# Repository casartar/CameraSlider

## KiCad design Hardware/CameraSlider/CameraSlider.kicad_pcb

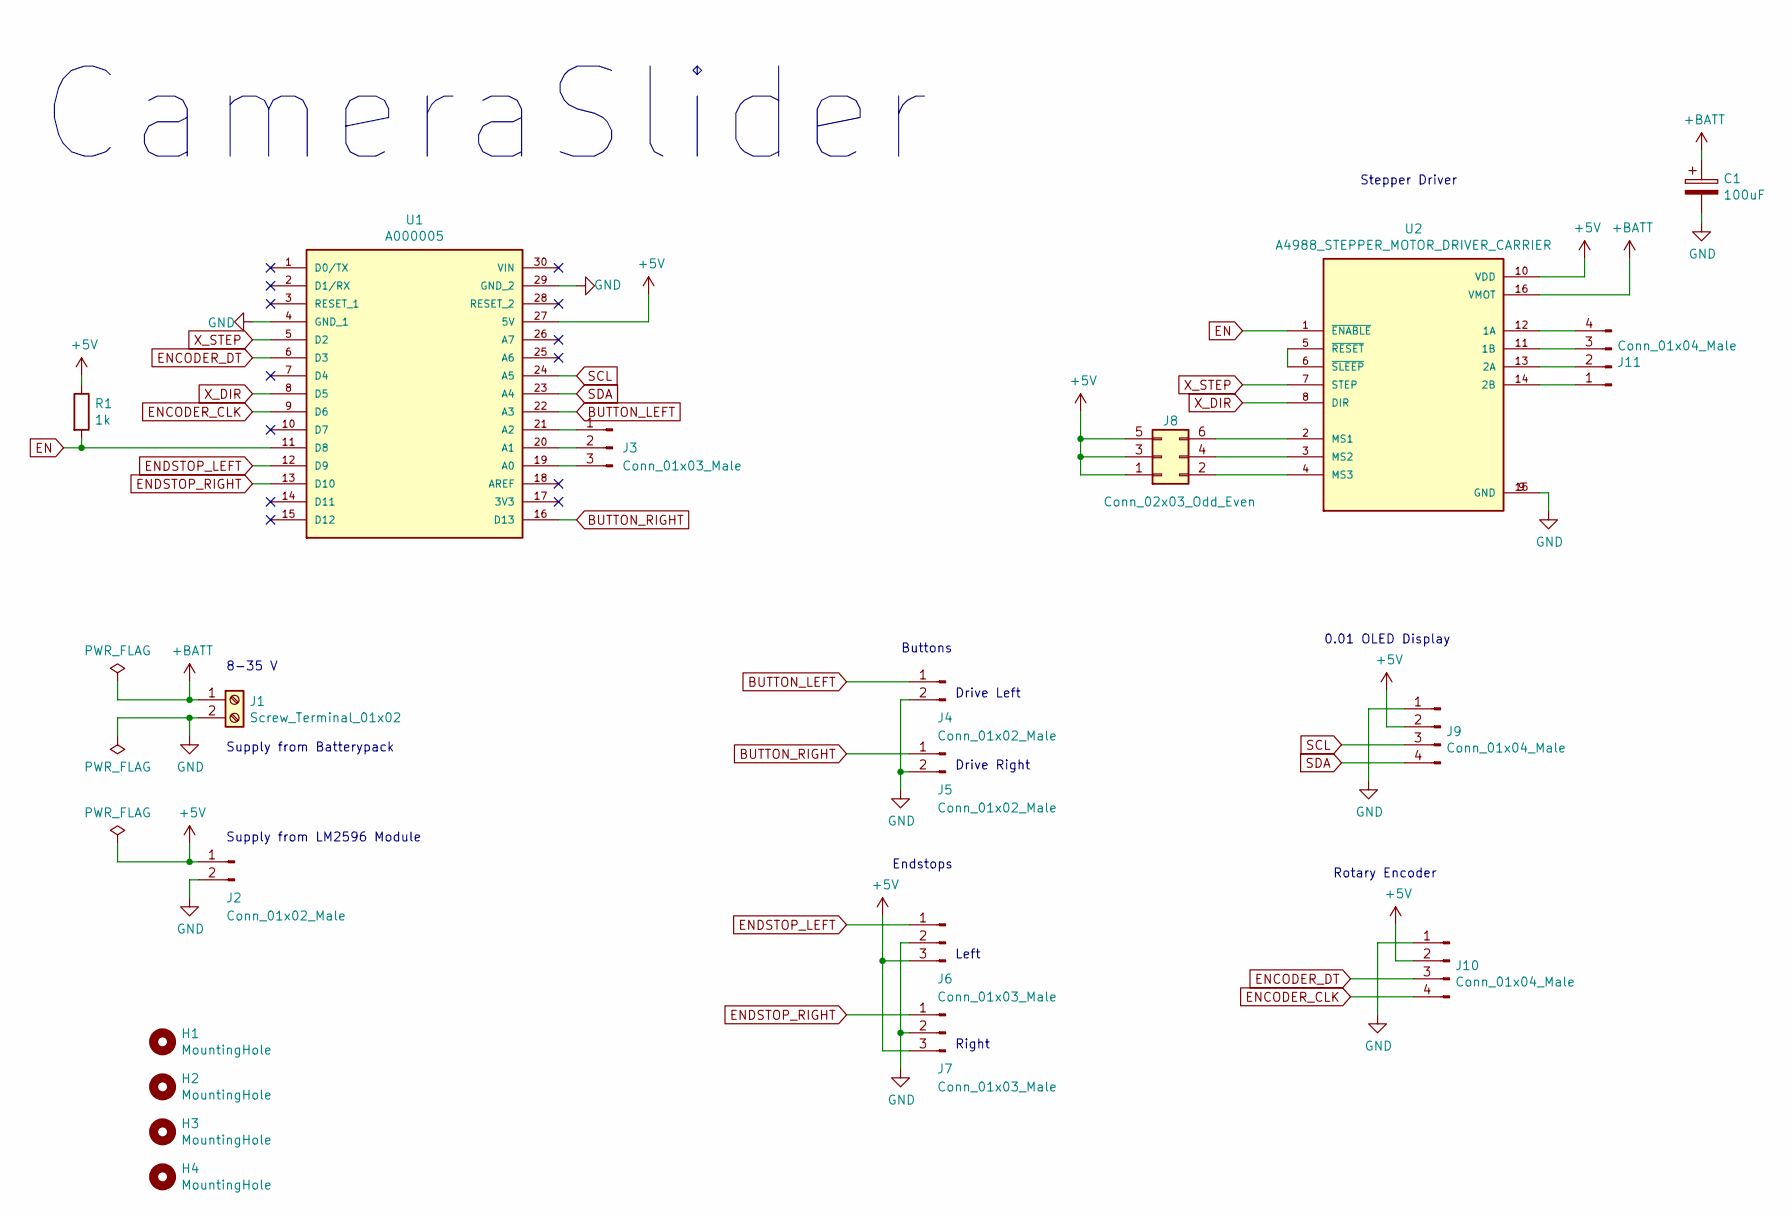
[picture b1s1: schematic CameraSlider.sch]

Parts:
C1: 100uF; CP_Radial_D8.0mm_P2.50mm
H1, H2, H3, H4: MountingHole; MountingHole_3.2mm_M3_Pad
J1: Screw_Terminal_01x02; TerminalBlock_Altech_AK300-2_P5.00mm
J2, J4, J5: Conn_01x02_Male; Pin_Header_Angled_1x02_Pitch2.54mm
J3: Conn_01x03_Male; Pin_Header_Straight_1x03_Pitch2.54mm
J6, J7: Conn_01x03_Male; Pin_Header_Angled_1x03_Pitch2.54mm
J8: Conn_02x03_Odd_Even; Pin_Header_Straight_2x03_Pitch2.54mm
J9, J10, J11: Conn_01x04_Male; Pin_Header_Angled_1x04_Pitch2.54mm
R1: 1k; R_Axial_DIN0207_L6.3mm_D2.5mm_P7.62mm_Horizontal
U1: A000005; MODULE_A000005; PARTREV 23/03/2020
U2: A4988_STEPPER_MOTOR_DRIVER_CARRIER; MODULE_A4988_STEPPER_MOTOR_DRIVER_CARRIER

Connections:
+5V: J2.1, J6.3, J7.3, J8.1, J8.3, J8.5, J9.2, J10.2, R1.1, U1.27 (5V), U2.10 (VDD)
+BATT: C1.1, J1.1, U2.16 (VMOT)
BUTTON_LEFT: J4.1, U1.22 (A3)
BUTTON_RIGHT: J5.1, U1.16 (D13)
EN: R1.2, U1.11 (D8), U2.1 (~ENABLE)
ENCODER_CLK: J10.4, U1.9 (D6)
ENCODER_DT: J10.3, U1.6 (D3)
ENDSTOP_LEFT: J6.1, U1.12 (D9)
ENDSTOP_RIGHT: J7.1, U1.13 (D10)
GND: C1.2, J1.2, J2.2, J4.2, J5.2, J6.2, J7.2, J9.1, J10.1, U1.4 (GND_1), U1.29 (GND_2), U2.9 (GND), U2.15 (GND)
unnamed: J3.1, U1.21 (A2)
unnamed: J3.2, U1.20 (A1)
unnamed: J3.3, U1.19 (A0)
unnamed: J8.2, U2.4 (MS3)
unnamed: J8.4, U2.3 (MS2)
unnamed: J8.6, U2.2 (MS1)
unnamed: J11.1, U2.14 (2B)
unnamed: J11.2, U2.13 (2A)
unnamed: J11.3, U2.11 (1B)
unnamed: J11.4, U2.12 (1A)
unnamed: U2.5 (~RESET), U2.6 (~SLEEP)
SCL: J9.3, U1.24 (A5)
SDA: J9.4, U1.23 (A4)
X_DIR: U1.8 (D5), U2.8 (DIR)
X_STEP: U1.5 (D2), U2.7 (STEP)

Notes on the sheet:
0.01 OLED Display
Stepper Driver
Rotary Encoder
Buttons
Endstops
Drive Left
Drive Right
Left
Right
CameraSlider
8-35 V
Supply from Batterypack
Supply from LM2596 Module

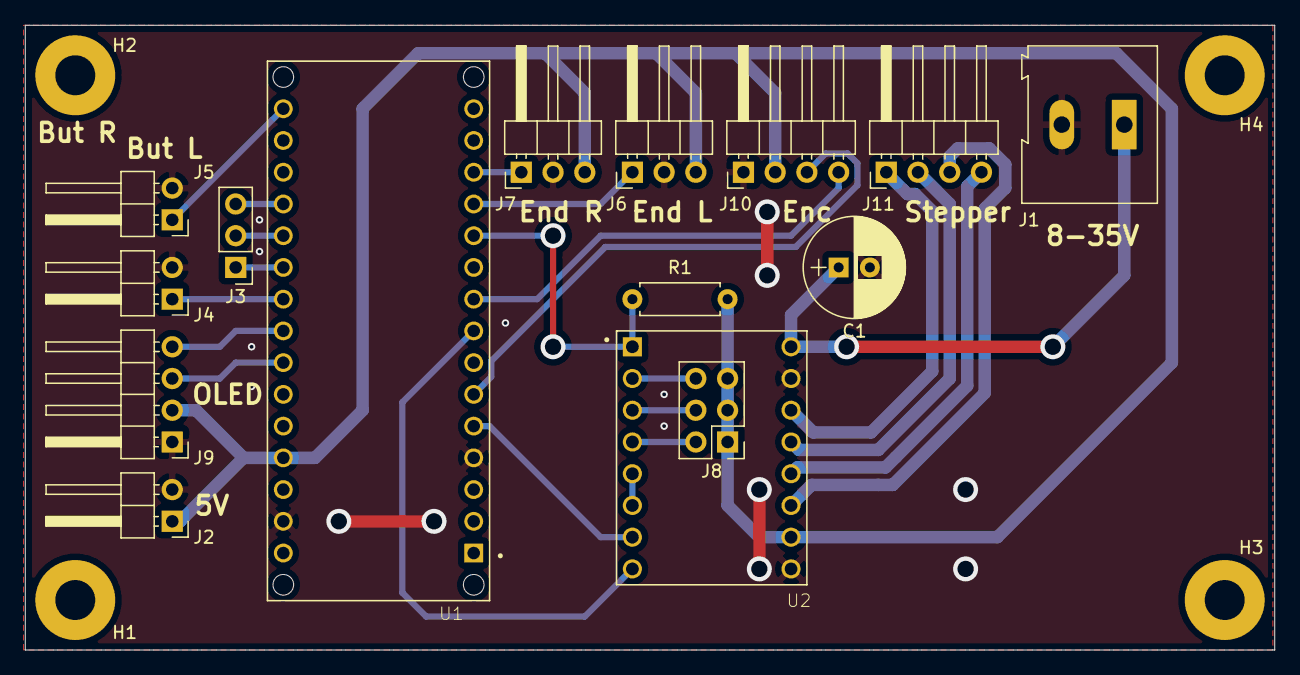
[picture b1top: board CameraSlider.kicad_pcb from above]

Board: 2 copper layers, 100.0 x 50.0 mm, 19 parts (0 on the bottom side), 25 nets.

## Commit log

2021-06-18 Menü als struct, statemachine
2021-06-19 Hardware PCB Schematic hinzugefügt
2021-06-20 Layout hinzugefügt
2021-06-20 Clearence vergrößert und GND Drahtbrücke hinzugefügt
2021-06-26 Stepper enable invertiert
2022-05-29 add Gerbers
